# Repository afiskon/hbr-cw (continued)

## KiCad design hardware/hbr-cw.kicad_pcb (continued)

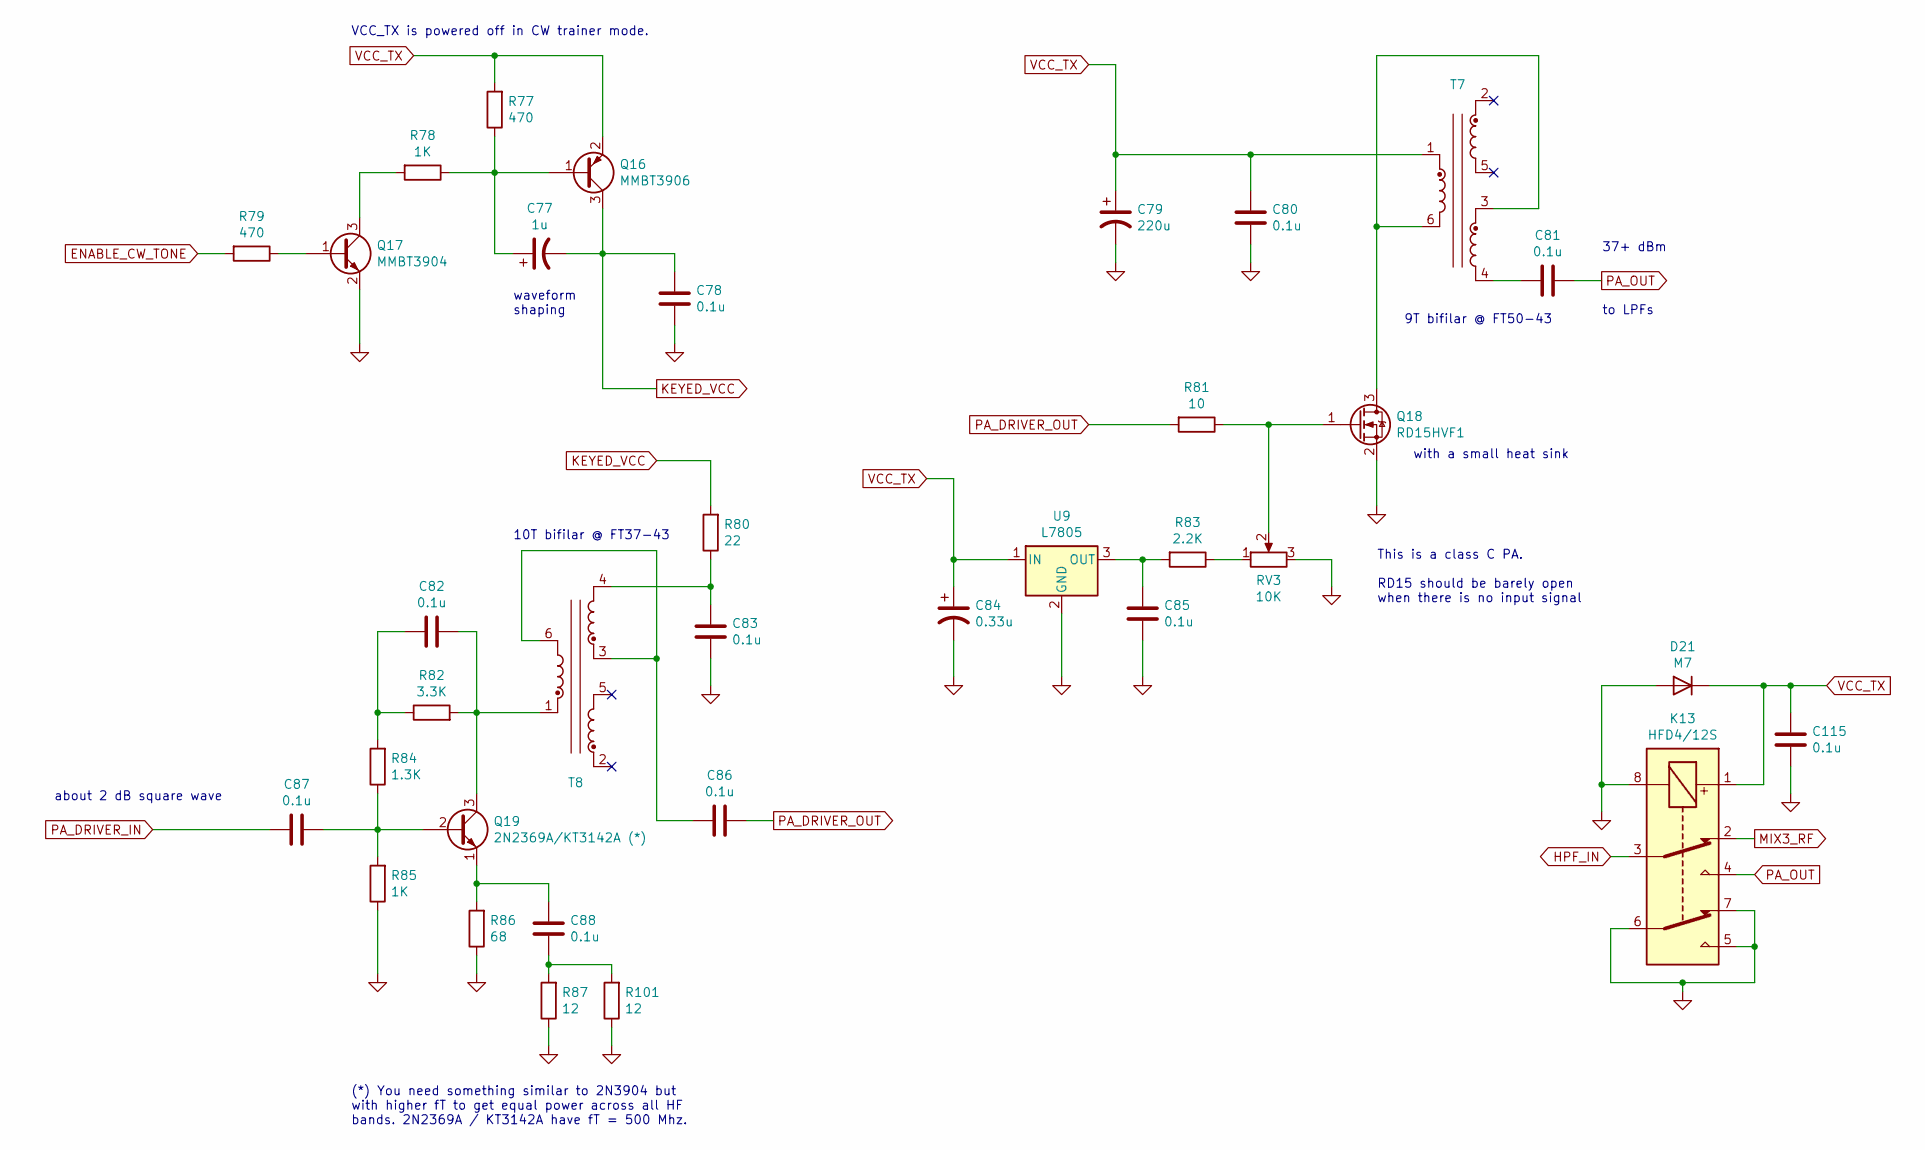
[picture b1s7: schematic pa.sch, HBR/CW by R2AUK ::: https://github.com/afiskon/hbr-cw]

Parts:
C77: 1u; CP_Elec_4x5.4
C78, C80, C81, C82, C83, C85, C86, C87, C88, C115: 0.1u; C_0805_2012Metric_Pad1.15x1.40mm_HandSolder
C79: 220u; CP_Elec_8x10.5
C84: 0.33u; C_Radial_D5.0mm_H5.0mm_P2.00mm
D21: M7; D_SMA_Handsoldering
K13: HFD4/12S; Relay_DPDT_Omron_G6K-2F-Y
Q16: MMBT3906; SOT-23
Q17: MMBT3904; SOT-23
Q18: RD15HVF1; TO-220-3_Vertical
Q19: 2N2369A/КТ3142A (*); TO-18-3
R77, R79: 470; R_0805_2012Metric_Pad1.15x1.40mm_HandSolder
R78, R85: 1K; R_0805_2012Metric_Pad1.15x1.40mm_HandSolder
R80: 22; R_0805_2012Metric_Pad1.15x1.40mm_HandSolder
R81: 10; R_0805_2012Metric_Pad1.15x1.40mm_HandSolder
R82: 3.3K; R_0805_2012Metric_Pad1.15x1.40mm_HandSolder
R83: 2.2K; R_0805_2012Metric_Pad1.15x1.40mm_HandSolder
R84: 1.3K; R_0805_2012Metric_Pad1.15x1.40mm_HandSolder
R86: 68; R_0805_2012Metric_Pad1.15x1.40mm_HandSolder
R87, R101: 12; R_0805_2012Metric_Pad1.15x1.40mm_HandSolder
RV3: 10K; Potentiometer_Bourns_3296W_Vertical
T7: FT50-43; DIP-6_W7.62mm
T8: FT37-43; DIP-6_W7.62mm
U9: L7805; TO-263-2

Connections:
ENABLE_CW_TONE: R79.2; also elsewhere on the board
GND: C78.1, C79.2, C80.2, C83.1, C84.2, C85.2, C115.2, D21.2 (A), K13.5, K13.6, K13.7, K13.8, Q17.2 (E), Q18.2 (S), R85.1, R86.1, R87.1, R101.1, RV3.3, U9.2 (GND); also elsewhere on the board
HPF_IN: K13.3; also elsewhere on the board
KEYED_VCC: C77.2, C78.2, Q16.3 (C), R80.2
MIX3_RF: K13.2; also elsewhere on the board
unnamed: C77.1, Q16.1 (B), R77.1, R78.1
unnamed: C81.2, T7.4
unnamed: C82.1, Q19.3 (C), R82.2, T8.1
unnamed: C82.2, R82.1, R84.2
unnamed: C83.2, R80.1, T8.4
unnamed: C85.1, R83.2, U9.3 (OUT)
unnamed: C86.2, T8.3, T8.6
unnamed: C87.1, Q19.2 (B), R84.1, R85.2
unnamed: C88.1, R87.2, R101.2
unnamed: C88.2, Q19.1 (E), R86.2
unnamed: Q17.1 (B), R79.1
unnamed: Q17.3 (C), R78.2
unnamed: Q18.1 (G), R81.1, RV3.2
unnamed: Q18.3 (D), T7.3, T7.6
unnamed: R83.1, RV3.1
PA_DRIVER_IN: C87.2; also elsewhere on the board
PA_DRIVER_OUT: C86.1, R81.2
PA_OUT: C81.1, K13.4
VCC_TX: C79.1, C80.1, C84.1, C115.1, D21.1 (K), K13.1, Q16.2 (E), R77.2, T7.1, U9.1 (IN); also elsewhere on the board

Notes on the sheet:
about 2 dB square wave
10T bifilar @ FT37-43
(*) You need something similar to 2N3904 but with higher fT to get equal power across all HF bands. 2N2369A / KT3142A have fT = 500 Mhz.
waveform shaping
with a small heat sink
9T bifilar @ FT50-43
to LPFs
This is a class C PA. RD15 should be barely open when there is no input signal
37+ dBm
VCC_TX is powered off in CW trainer mode.

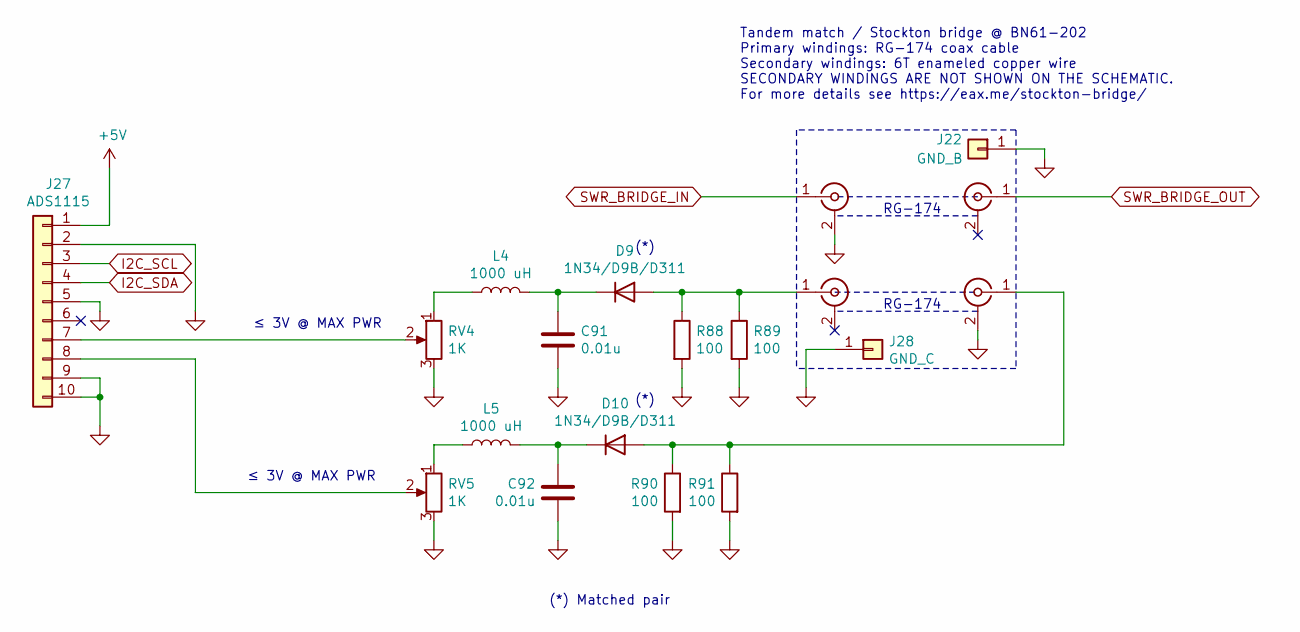
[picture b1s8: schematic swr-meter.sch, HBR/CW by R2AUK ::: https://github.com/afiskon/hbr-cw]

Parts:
C91, C92: 0.01u; C_0805_2012Metric_Pad1.15x1.40mm_HandSolder
D9, D10: 1N34/D9B/D311; D_DO-41_SOD81_P10.16mm_Horizontal
J22: GND_B; PinHeader_1x01_P2.54mm_Vertical
J23: STK_A; PinHeader_1x02_P2.54mm_Vertical
J24: STK_B; PinHeader_1x02_P2.54mm_Vertical
J25: STK_C; PinHeader_1x02_P2.54mm_Vertical
J26: STK_D; PinHeader_1x02_P2.54mm_Vertical
J27: ADS1115; PinSocket_1x10_P2.54mm_Vertical
J28: GND_C; PinHeader_1x01_P2.54mm_Vertical
L4, L5: 1000 uH; L_Axial_L6.6mm_D2.7mm_P10.16mm_Horizontal_Vishay_IM-2
R88, R89, R90, R91: 100; R_0805_2012Metric_Pad1.15x1.40mm_HandSolder
RV4, RV5: 1K; Potentiometer_Bourns_3296W_Vertical

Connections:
+5V: J27.1; also elsewhere on the board
GND: C91.2, C92.2, J22.1, J23.2 (Ext), J26.2 (Ext), J27.2, J27.5, J27.9, J27.10, J28.1, R88.2, R89.2, R90.2, R91.2, RV4.3, RV5.3; also elsewhere on the board
I2C_SCL: J27.3; also elsewhere on the board
I2C_SDA: J27.4; also elsewhere on the board
unnamed: C91.1, D9.1 (K), L4.2
unnamed: C92.1, D10.1 (K), L5.1
unnamed: D9.2 (A), J25.1 (In), R88.1, R89.1
unnamed: D10.2 (A), J26.1 (In), R90.1, R91.1
unnamed: J27.7, RV4.2
unnamed: J27.8, RV5.2
unnamed: L4.1, RV4.1
unnamed: L5.2, RV5.1
SWR_BRIDGE_IN: J23.1 (In); also elsewhere on the board
SWR_BRIDGE_OUT: J24.1 (In); also elsewhere on the board

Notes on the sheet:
Tandem match / Stockton bridge @ BN61-202 Primary windings: RG-174 coax cable Secondary windings: 6T enameled copper wire SECONDARY WINDINGS ARE NOT SHOWN ON THE SCHEMATIC. For more details see https://eax.me/stockton-bridge/
RG-174
≤ 3V @ MAX PWR
(*)
(*) Matched pair

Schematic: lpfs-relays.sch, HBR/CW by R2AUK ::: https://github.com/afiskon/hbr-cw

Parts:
C89, C90: 1000p; C_0805_2012Metric_Pad1.15x1.40mm_HandSolder
C93, C94, C95, C96, C97, C98, C99, C100, C101, C102, C103, C104, C105, C106, C107, C108, C109, C110, C113, C114: 0.1u; C_0805_2012Metric_Pad1.15x1.40mm_HandSolder
D11, D12, D13, D14, D15, D16, D17, D18, D19, D20: M7; D_SMA_Handsoldering
K3, K4, K5, K6, K7, K8, K9, K10, K11, K12: HFD4/12S; Relay_DPDT_Omron_G6K-2F-Y
L6: 3.6u; L_Radial_L12.6mm_W12.6mm_Px9.52mm_Py9.52mm_Pulse_LP-37
Q20, Q21, Q22, Q23, Q24: MMBT3904; SOT-23
R92, R93, R94, R95, R96: 470; R_0805_2012Metric_Pad1.15x1.40mm_HandSolder

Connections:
GND: C93.2, C94.2, C95.2, C96.2, C97.2, C98.2, C99.2, C100.2, C101.2, C102.2, C103.2, C104.2, C105.2, C106.2, C107.2, C108.2, C109.2, C110.2, C113.2, C114.2, K3.5, K3.6, K3.7, K4.5, K4.6, K4.7, K5.5, K5.6, K5.7, K6.5, K6.6, K6.7, K7.5, K7.6, K7.7, K8.5, K8.6, K8.7, K9.5, K9.6, K9.7, K10.5, K10.6, K10.7, K11.5, K11.6, K11.7, K12.5, K12.6, K12.7, L6.2, Q20.2 (E), Q21.2 (E), Q22.2 (E), Q23.2 (E), Q24.2 (E); also elsewhere on the board
HPF_IN: C89.2; also elsewhere on the board
LPF10_CTL: C109.1, R96.2; also elsewhere on the board
LPF10_GND: D17.2 (A), D18.2 (A), K9.8, K10.8, Q24.3 (C)
LPF10_IN: K9.4; also elsewhere on the board
LPF10_OUT: K10.4; also elsewhere on the board
LPF15_CTL: C107.1, R95.2; also elsewhere on the board
LPF15_GND: D13.2 (A), D14.2 (A), K5.8, K6.8, Q23.3 (C)
LPF15_IN: K5.4; also elsewhere on the board
LPF15_OUT: K6.4; also elsewhere on the board
LPF20_CTL: C101.1, R94.2; also elsewhere on the board
LPF20_GND: D19.2 (A), D20.2 (A), K11.8, K12.8, Q22.3 (C)
LPF20_IN: K11.4; also elsewhere on the board
LPF20_OUT: K12.4; also elsewhere on the board
LPF40_CTL: C99.1, R93.2; also elsewhere on the board
LPF40_GND: D15.2 (A), D16.2 (A), K7.8, K8.8, Q21.3 (C)
LPF40_IN: K7.4; also elsewhere on the board
LPF40_OUT: K8.4; also elsewhere on the board
LPF80_CTL: C97.1, R92.2; also elsewhere on the board
LPF80_GND: D11.2 (A), D12.2 (A), K3.8, K4.8, Q20.3 (C)
LPF80_IN: K3.4; also elsewhere on the board
LPF80_OUT: K4.4; also elsewhere on the board
LPFS_IN: C90.1, K3.3, K5.3, K7.3, K9.3, K11.3
unnamed: C89.1, C90.2, L6.1
unnamed: C98.1, Q20.1 (B), R92.1
unnamed: C100.1, Q21.1 (B), R93.1
unnamed: C102.1, Q22.1 (B), R94.1
unnamed: C108.1, Q23.1 (B), R95.1
unnamed: C110.1, Q24.1 (B), R96.1
SWR_BRIDGE_IN: K4.3, K6.3, K8.3, K10.3, K12.3; also elsewhere on the board
VCC: C93.1, C94.1, C95.1, C96.1, C103.1, C104.1, C105.1, C106.1, C113.1, C114.1, D11.1 (K), D12.1 (K), D13.1 (K), D14.1 (K), D15.1 (K), D16.1 (K), D17.1 (K), D18.1 (K), D19.1 (K), D20.1 (K), K3.1, K4.1, K5.1, K6.1, K7.1, K8.1, K9.1, K10.1, K11.1, K12.1; also elsewhere on the board

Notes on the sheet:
1 MHz HPF (optional) 3.6u = 20T @ 2 x T50-6 = 25T @ T68-2

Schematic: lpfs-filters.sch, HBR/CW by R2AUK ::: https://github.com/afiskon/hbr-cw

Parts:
C116, C117, C127, C128, C177, C187: 470p; C_0805_2012Metric_Pad1.15x1.40mm_HandSolder
C119, C120, C124, C125, C179, C181, C185: 820p; C_0805_2012Metric_Pad1.15x1.40mm_HandSolder
C121, C123: 680p; C_0805_2012Metric_Pad1.15x1.40mm_HandSolder
C122: 390p; C_0805_2012Metric_Pad1.15x1.40mm_HandSolder
C131, C143, C165, C170: 150p; C_0805_2012Metric_Pad1.15x1.40mm_HandSolder
C132, C135, C139, C142, C150, C154: 10p; C_0805_2012Metric_Pad1.15x1.40mm_HandSolder
C134, C136, C140, C164, C169: 270p; C_0805_2012Metric_Pad1.15x1.40mm_HandSolder
C137, C180, C184: 22p; C_0805_2012Metric_Pad1.15x1.40mm_HandSolder
C146, C148, C149, C155, C156, C158: 100p; C_0805_2012Metric_Pad1.15x1.40mm_HandSolder
C147, C157, C162, C172: 18p; C_0805_2012Metric_Pad1.15x1.40mm_HandSolder
C152, C161, C166, C168, C173: 220p; C_0805_2012Metric_Pad1.15x1.40mm_HandSolder
C182: 56p; C_0805_2012Metric_Pad1.15x1.40mm_HandSolder
L7, L10: 2.9u; L_Radial_L12.6mm_W12.6mm_Px9.52mm_Py9.52mm_Pulse_LP-37
L8, L9: 3.2u; L_Radial_L12.6mm_W12.6mm_Px9.52mm_Py9.52mm_Pulse_LP-37
L11, L14: 0.5u; L_Toroid_Vertical_L13.0mm_W6.5mm_P5.60mm
L12, L13: 0.6u; L_Toroid_Vertical_L13.0mm_W6.5mm_P5.60mm
L15, L18: 0.35u; L_Toroid_Vertical_L13.0mm_W6.5mm_P5.60mm
L16, L17: 0.4u; L_Toroid_Vertical_L13.0mm_W6.5mm_P5.60mm
L19, L22: 0.7u; L_Toroid_Vertical_L13.0mm_W6.5mm_P5.60mm
L20, L21: 0.8u; L_Toroid_Vertical_L13.0mm_W6.5mm_P5.60mm
L23, L26: 1.4u; L_Toroid_Vertical_L13.0mm_W6.5mm_P5.60mm
L24, L25: 1.6u; L_Toroid_Vertical_L13.0mm_W6.5mm_P5.60mm

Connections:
GND: C116.2, C117.2, C119.2, C120.2, C121.2, C122.2, C123.2, C124.2, C125.2, C127.2, C128.2, C131.2, C132.2, C134.2, C135.2, C136.2, C137.2, C139.2, C140.2, C142.2, C143.2, C146.2, C147.2, C148.2, C149.2, C150.2, C152.2, C154.2, C155.2, C156.2, C157.2, C158.2, C161.2, C162.2, C164.2, C165.2, C166.2, C168.2, C169.2, C170.2, C172.2, C173.2, C177.2, C179.2, C180.2, C181.2, C182.2, C184.2, C185.2, C187.2; also elsewhere on the board
LPF10_IN: C146.1, C147.1, L15.1; also elsewhere on the board
LPF10_OUT: C157.1, C158.1, L18.1; also elsewhere on the board
LPF15_IN: C131.1, C132.1, L11.1; also elsewhere on the board
LPF15_OUT: C142.1, C143.1, L14.1; also elsewhere on the board
LPF20_IN: C161.1, C162.1, L19.1; also elsewhere on the board
LPF20_OUT: C172.1, C173.1, L22.1; also elsewhere on the board
LPF40_IN: C177.1, L23.1; also elsewhere on the board
LPF40_OUT: C187.1, L26.1; also elsewhere on the board
LPF80_IN: C116.1, C117.1, L7.1; also elsewhere on the board
LPF80_OUT: C127.1, C128.1, L10.1; also elsewhere on the board
unnamed: C119.1, C120.1, L7.2, L8.1
unnamed: C121.1, C122.1, C123.1, L8.2, L9.2
unnamed: C124.1, C125.1, L9.1, L10.2
unnamed: C134.1, C135.1, L11.2, L12.1
unnamed: C136.1, C137.1, L12.2, L13.2
unnamed: C139.1, C140.1, L13.1, L14.2
unnamed: C148.1, C149.1, C150.1, L15.2, L16.1
unnamed: C152.1, L16.2, L17.2
unnamed: C154.1, C155.1, C156.1, L17.1, L18.2
unnamed: C164.1, C165.1, L19.2, L20.1
unnamed: C166.1, C168.1, L20.2, L21.2
unnamed: C169.1, C170.1, L21.1, L22.2
unnamed: C179.1, C180.1, L23.2, L24.1
unnamed: C181.1, C182.1, L24.2, L25.2
unnamed: C184.1, C185.1, L25.1, L26.2

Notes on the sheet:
2.9u = 18T @ 2x T50-6 = 21T @ T68-2
3.2u = 19T @ 2x T50-6 = 23T @ T68-2
0.5u = 10T @ T50-6
0.6u = 11T @ T50-6
0.35u = 8T @ T50-6
0.40u = 9T @ T50-6
0.7u = 12T @ T50-6
0.8u = 13T @ T50-6
1.4u = 18T @ T50-6
1.6u = 19T @ T50-6

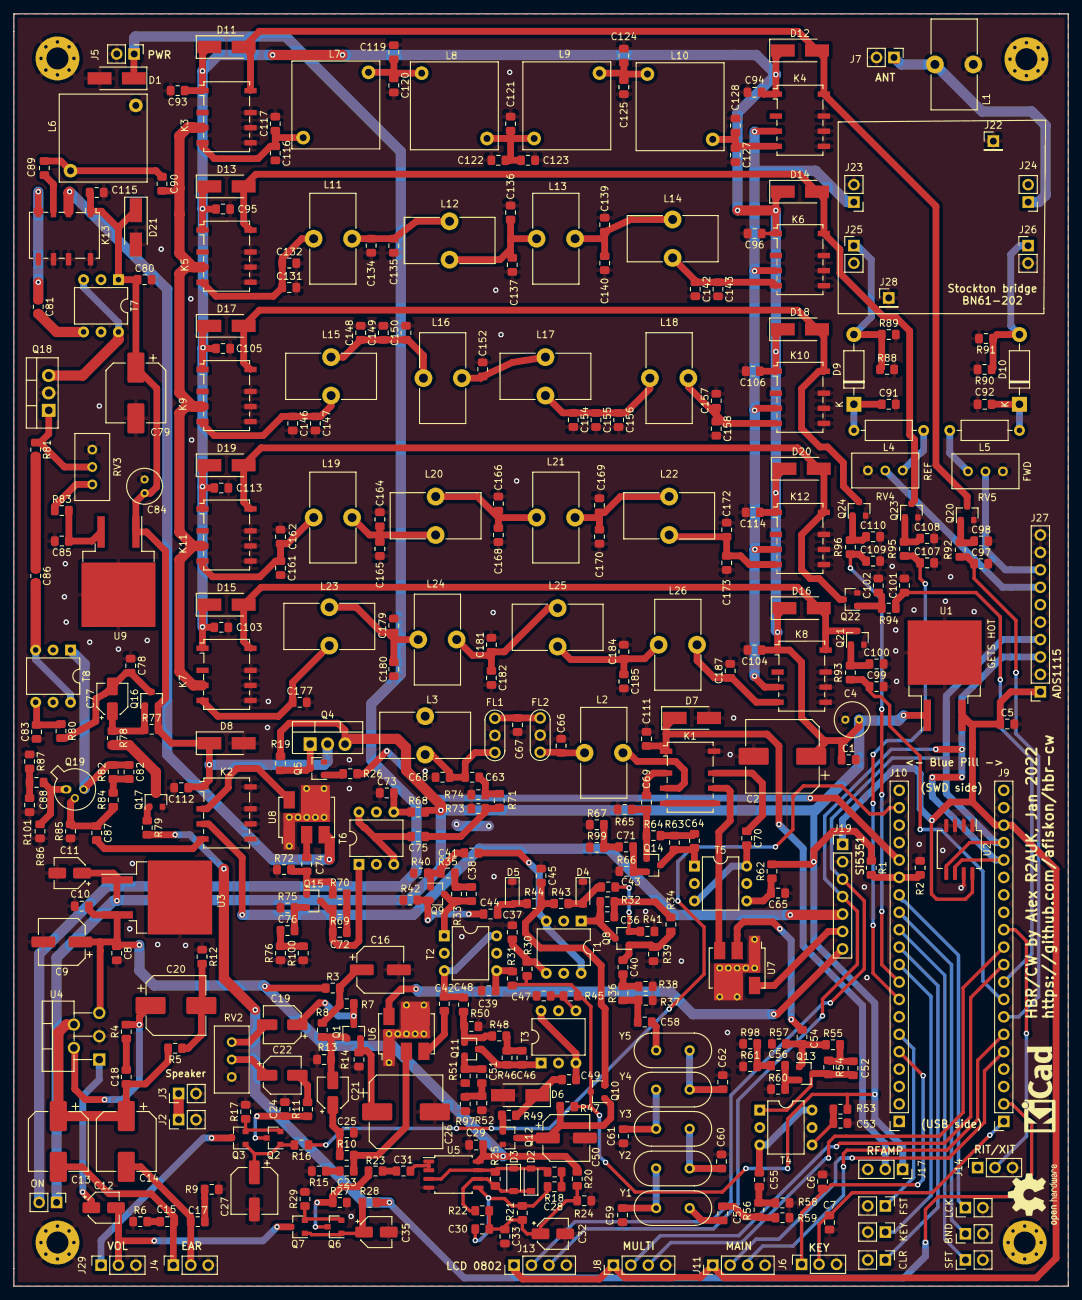
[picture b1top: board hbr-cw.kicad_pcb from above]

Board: 2 copper layers, 153.7 x 185.4 mm, 411 parts (0 on the bottom side), 209 nets.

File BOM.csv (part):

Reference, Quantity, Value, Footprint
C1 C5 C6 C7 C8 C10 C15 C17 C29 C31 C33 C36 C37 C38 C39 C40 C41 C42 C43 C44 C45 C46 C47 C49 C51 C52 C53 C54 C55 C56 C64 C65 C69 C70 C71 C72 C73 C74 C75 C76 C78 C80 C81 C82 C83 C85 C86 C87 C88 C93 C94 C95 C96 C97 C98 C99 C100 C101 C102 C103 C104 C105 C106 C107 C108 C109 C110 C111 C112 C113 C114 C115 ,72,0.1u,Capacitor_SMD:C_0805_2012Metric_Pad1.15x1.40mm_HandSolder
C11 C21 C32 ,3,10u,Capacitor_SMD:CP_Elec_4x5.4
C119 C120 C124 C125 C179 C181 C185 ,7,820p,Capacitor_SMD:C_0805_2012Metric_Pad1.15x1.40mm_HandSolder
C12 C77 ,2,1u,Capacitor_SMD:CP_Elec_4x5.4
C121 C123 ,2,680p,Capacitor_SMD:C_0805_2012Metric_Pad1.15x1.40mm_HandSolder
C122 ,1,390p,Capacitor_SMD:C_0805_2012Metric_Pad1.15x1.40mm_HandSolder
C131 C143 C165 C170 ,4,150p,Capacitor_SMD:C_0805_2012Metric_Pad1.15x1.40mm_HandSolder
C132 C135 C139 C142 C150 C154 ,6,10p,Capacitor_SMD:C_0805_2012Metric_Pad1.15x1.40mm_HandSolder
C146 C148 C149 C155 C156 C158 ,6,100p,Capacitor_SMD:C_0805_2012Metric_Pad1.15x1.40mm_HandSolder
C147 C157 C162 C172 ,4,18p,Capacitor_SMD:C_0805_2012Metric_Pad1.15x1.40mm_HandSolder
C152 C161 C166 C168 C173 ,5,220p,Capacitor_SMD:C_0805_2012Metric_Pad1.15x1.40mm_HandSolder
C18 C24 C25 ,3,47n,Capacitor_SMD:C_0805_2012Metric_Pad1.15x1.40mm_HandSolder
C182 ,1,56p,Capacitor_SMD:C_0805_2012Metric_Pad1.15x1.40mm_HandSolder
C19 C22 ,2,22u,Capacitor_SMD:CP_Elec_5x5.4
C2 C26 ,2,470u,Capacitor_SMD:CP_Elec_10x10.5
C13 C14 C20 C79 ,4,220u,Capacitor_SMD:CP_Elec_8x10.5
C23 C91 C92 ,3,0.01u,Capacitor_SMD:C_0805_2012Metric_Pad1.15x1.40mm_HandSolder
C27 ,1,47u,Capacitor_SMD:CP_Elec_6.3x5.8
C28 C30 ,2,4.7n,Capacitor_SMD:C_0805_2012Metric_Pad1.15x1.40mm_HandSolder
C35 ,1,4.7u,Capacitor_SMD:CP_Elec_4x5.4
C4 C84 ,2,0.33u,Capacitor_THT:C_Radial_D5.0mm_H5.0mm_P2.00mm
C48 C116 C117 C127 C128 C177 C187 ,7,470p,Capacitor_SMD:C_0805_2012Metric_Pad1.15x1.40mm_HandSolder
C57 C58 C59 C60 C61 C62 C134 C136 C140 C164 C169 ,11,270p,Capacitor_SMD:C_0805_2012Metric_Pad1.15x1.40mm_HandSolder
C63 C66 C137 C180 C184 ,5,22p,Capacitor_SMD:C_0805_2012Metric_Pad1.15x1.40mm_HandSolder
C67 ,1,8p,Capacitor_SMD:C_0805_2012Metric_Pad1.15x1.40mm_HandSolder
C68 ,1,2p,Capacitor_SMD:C_0805_2012Metric_Pad1.15x1.40mm_HandSolder
C89 C90 ,2,1000p,Capacitor_SMD:C_0805_2012Metric_Pad1.15x1.40mm_HandSolder
C9 C16 C50 ,3,100u,Capacitor_SMD:CP_Elec_6.3x7.7
D1 D6 ,2,SS14,Diode_SMD:D_SMA_Handsoldering
D9 D10 ,2,1N34/D9B/D311,Diode_THT:D_DO-41_SOD81_P10.16mm_Horizontal
D2 D3 D4 D5 ,4,1N4148W,Diode_SMD:D_SOD-123
D7 D8 D11 D12 D13 D14 D15 D16 D17 D18 D19 D20 D21 ,13,M7,Diode_SMD:D_SMA_Handsoldering
FL1 FL2 ,2,45M15B (*),Crystal:Resonator-3Pin_W7.0mm_H2.5mm
H1 H2 H3 H4 ,4,MH,MountingHole:MountingHole_3.2mm_M3_Pad_Via
J1 ,1,ON/OFF,Connector_PinHeader_2.54mm:PinHeader_1x02_P2.54mm_Vertical
J10 ,1,BluePill_Right,Connector_PinSocket_2.54mm:PinSocket_1x20_P2.54mm_Vertical
J11 ,1,MAIN,Connector_PinHeader_2.54mm:PinHeader_1x04_P2.54mm_Vertical
J12 ,1,BAND,Connector_PinHeader_2.54mm:PinHeader_1x02_P2.54mm_Vertical
J13 ,1,LCD 0802,Connector_PinHeader_2.54mm:PinHeader_1x04_P2.54mm_Vertical
J14 ,1,RIT/XIT,Connector_PinSocket_2.54mm:PinSocket_1x03_P2.54mm_Vertical
J15 ,1,FAST,Connector_PinHeader_2.54mm:PinHeader_1x02_P2.54mm_Vertical
J16 ,1,LOCK,Connector_PinHeader_2.54mm:PinHeader_1x02_P2.54mm_Vertical
J17 ,1,RFAMP,Connector_PinSocket_2.54mm:PinSocket_1x03_P2.54mm_Vertical
J18 ,1,CLAR,Connector_PinHeader_2.54mm:PinHeader_1x02_P2.54mm_Vertical
J19 ,1,Si5351,Connector_PinHeader_2.54mm:PinHeader_1x07_P2.54mm_Vertical
J2 ,1,SPEAKER_IN,Connector_PinHeader_2.54mm:PinHeader_1x02_P2.54mm_Vertical
J20 ,1,SHIFT,Connector_PinHeader_2.54mm:PinHeader_1x02_P2.54mm_Vertical
J21 ,1,KEYER,Connector_PinHeader_2.54mm:PinHeader_1x02_P2.54mm_Vertical
J22 ,1,GND_B,Connector_PinHeader_2.54mm:PinHeader_1x01_P2.54mm_Vertical
J23 ,1,STK_A,Connector_PinHeader_2.54mm:PinHeader_1x02_P2.54mm_Vertical
J24 ,1,STK_B,Connector_PinHeader_2.54mm:PinHeader_1x02_P2.54mm_Vertical
J25 ,1,STK_C,Connector_PinHeader_2.54mm:PinHeader_1x02_P2.54mm_Vertical
J26 ,1,STK_D,Connector_PinHeader_2.54mm:PinHeader_1x02_P2.54mm_Vertical
J27 ,1,ADS1115,Connector_PinSocket_2.54mm:PinSocket_1x10_P2.54mm_Vertical
J28 ,1,GND_C,Connector_PinHeader_2.54mm:PinHeader_1x01_P2.54mm_Vertical
J29 ,1,VOL,Connector_PinSocket_2.54mm:PinSocket_1x03_P2.54mm_Vertical
J3 ,1,SPEAKER_OUT,Connector_PinHeader_2.54mm:PinHeader_1x02_P2.54mm_Vertical
J4 ,1,EAR,Connector_PinSocket_2.54mm:PinSocket_1x03_P2.54mm_Vertical
J5 ,1,VCC,Connector_PinHeader_2.54mm:PinHeader_1x02_P2.54mm_Vertical
J6 ,1,KEY,Connector_PinSocket_2.54mm:PinSocket_1x03_P2.54mm_Vertical
J7 ,1,ANT,Connector_PinHeader_2.54mm:PinHeader_1x02_P2.54mm_Vertical
J8 ,1,MULTI,Connector_PinHeader_2.54mm:PinHeader_1x04_P2.54mm_Vertical
J9 ,1,BluePill_Left,Connector_PinSocket_2.54mm:PinSocket_1x20_P2.54mm_Vertical
K1 K2 K3 K4 K5 K6 K7 K8 K9 K10 K11 K12 K13 ,13,HFD4/12S,Relay_SMD:Relay_DPDT_Omron_G6K-2F-Y
L1 ,1,23T @ FT50-43,Inductor_THT:L_Toroid_Vertical_L13.0mm_W6.5mm_P5.60mm
L11 L14 ,2,0.5u,Inductor_THT:L_Toroid_Vertical_L13.0mm_W6.5mm_P5.60mm
L15 L18 ,2,0.35u,Inductor_THT:L_Toroid_Vertical_L13.0mm_W6.5mm_P5.60mm
L16 L17 ,2,0.4u,Inductor_THT:L_Toroid_Vertical_L13.0mm_W6.5mm_P5.60mm
L19 L22 ,2,0.7u,Inductor_THT:L_Toroid_Vertical_L13.0mm_W6.5mm_P5.60mm
L2 L12 L13 ,3,0.6u,Inductor_THT:L_Toroid_Vertical_L13.0mm_W6.5mm_P5.60mm
L20 L21 ,2,0.8u,Inductor_THT:L_Toroid_Vertical_L13.0mm_W6.5mm_P5.60mm
L23 L26 ,2,1.4u,Inductor_THT:L_Toroid_Vertical_L13.0mm_W6.5mm_P5.60mm
L24 L25 ,2,1.6u,Inductor_THT:L_Toroid_Vertical_L13.0mm_W6.5mm_P5.60mm
L3 ,1,0.65u,Inductor_THT:L_Toroid_Vertical_L13.0mm_W6.5mm_P5.60mm
L4 L5 ,2,1000 uH,Inductor_THT:L_Axial_L6.6mm_D2.7mm_P10.16mm_Horizontal_Vishay_IM-2
L6 ,1,3.6u,Inductor_THT:L_Radial_L12.6mm_W12.6mm_Px9.52mm_Py9.52mm_Pulse_LP-37
L7 L10 ,2,2.9u,Inductor_THT:L_Radial_L12.6mm_W12.6mm_Px9.52mm_Py9.52mm_Pulse_LP-37
L8 L9 ,2,3.2u,Inductor_THT:L_Radial_L12.6mm_W12.6mm_Px9.52mm_Py9.52mm_Pulse_LP-37
Q1 Q5 Q8 Q9 Q10 Q11 Q12 Q13 Q14 Q15 Q17 Q20 Q21 Q22 Q23 Q24 ,16,MMBT3904,Package_TO_SOT_SMD:SOT-23
Q16 ,1,MMBT3906,Package_TO_SOT_SMD:SOT-23
Q18 ,1,RD15HVF1,Package_TO_SOT_THT:TO-220-3_Vertical
Q19 ,1,2N2369A/КТ3142A (*),Package_TO_SOT_THT:TO-18-3
Q2 Q3 Q6 Q7 ,4,MMBF170,Package_TO_SOT_SMD:SOT-23
Q4 ,1,IRF4905,Package_TO_SOT_THT:TO-220-3_Vertical
R1 ,1,15K,Resistor_SMD:R_0805_2012Metric_Pad1.15x1.40mm_HandSolder
R6 R9 R12 R27 R81 ,5,10,Resistor_SMD:R_0805_2012Metric_Pad1.15x1.40mm_HandSolder
R13 ,1,47K,Resistor_SMD:R_0805_2012Metric_Pad1.15x1.40mm_HandSolder
R14 R39 R40 R43 R44 R50 R57 R65 R72 R78 R85 ,11,1K,Resistor_SMD:R_0805_2012Metric_Pad1.15x1.40mm_HandSolder
R15 ,1,51,Resistor_SMD:R_0805_2012Metric_Pad1.15x1.40mm_HandSolder
R7 R10 R11 R16 R28 R83 ,6,2.2K,Resistor_SMD:R_0805_2012Metric_Pad1.15x1.40mm_HandSolder
R17 R19 R29 ,3,10K,Resistor_SMD:R_0805_2012Metric_Pad1.15x1.40mm_HandSolder
R2 ,1,2.7K,Resistor_SMD:R_0805_2012Metric_Pad1.15x1.40mm_HandSolder
R18 R21 ,2,33K,Resistor_SMD:R_0805_2012Metric_Pad1.15x1.40mm_HandSolder
R22 R32 R33 R46 R54 R63 R69 R82 ,8,3.3K,Resistor_SMD:R_0805_2012Metric_Pad1.15x1.40mm_HandSolder
R23 ,1,6.8K,Resistor_SMD:R_0805_2012Metric_Pad1.15x1.40mm_HandSolder
R25 ,1,8.2K,Resistor_SMD:R_0805_2012Metric_Pad1.15x1.40mm_HandSolder
R26 R77 R79 R92 R93 R94 R95 R96 ,8,470,Resistor_SMD:R_0805_2012Metric_Pad1.15x1.40mm_HandSolder
R3 R30 R31 R88 R89 R90 R91 ,7,100,Resistor_SMD:R_0805_2012Metric_Pad1.15x1.40mm_HandSolder
R34 R35 ,2,820,Resistor_SMD:R_0805_2012Metric_Pad1.15x1.40mm_HandSolder
R36 ,1,18,Resistor_SMD:R_0805_2012Metric_Pad1.15x1.40mm_HandSolder
R37 R38 ,2,300,Resistor_SMD:R_0805_2012Metric_Pad1.15x1.40mm_HandSolder
R4 ,1,220,Resistor_SMD:R_0805_2012Metric_Pad1.15x1.40mm_HandSolder
R41 R42 R51 R60 R66 R75 R86 ,7,68,Resistor_SMD:R_0805_2012Metric_Pad1.15x1.40mm_HandSolder
R45 R53 R62 R68 R80 ,5,22,Resistor_SMD:R_0805_2012Metric_Pad1.15x1.40mm_HandSolder
R48 R55 R64 R70 R84 ,5,1.3K,Resistor_SMD:R_0805_2012Metric_Pad1.15x1.40mm_HandSolder
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
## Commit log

2022-04-17 Move the project from a sandbox repository
2022-04-17 Minor changes
2022-04-17 Add hardware/.gitignore
2022-04-17 A little clean up
2022-04-17 Tweak IF2Frequency a little
2022-04-17 Add firmware/si5351/README.md
2022-04-19 Update the silkscreen a little
2022-04-19 Add photos
2022-04-19 Minor change, update the URL in the sheets title
2022-04-19 Clarify that second IF can be other than 9 Mhz
2022-04-19 Add a block diagram
2022-04-23 Better spurs masking
2022-04-23 Even better spurs masking
2022-04-23 Look for SpurMaskInfo using binary search
2022-04-23 Further suppress spurs @ 80m
2022-04-23 Further suppress spurs @ 40m
2022-04-23 Fix FreqsWithSpurs list
2022-04-23 Check FreqsWithSpurs[] sort order + bugfix
2022-04-24 Fix FreqsWithSpurs[] sort order + some minor changes
2022-04-24 Further suppress spurs @ 30m
2022-04-24 Further suppress spurs @ 20m
2022-04-24 Further suppress spurs @ 17m
2022-04-24 Further suppress spurs @ 15m
2022-04-24 Further suppress spurs @ 10m
2022-04-24 Add a warning that U1 can get a little hot + minor changes
2022-04-24 Add maskInfo->useAlternativeIF2Frequency
2022-04-24 Further suppress spurs
2022-04-24 Fix syntax error
2022-04-24 Correct SpurMaskInfoArray[] sort order
2022-04-29 Remove the design implementation detail from README
    It can be changed in the future
